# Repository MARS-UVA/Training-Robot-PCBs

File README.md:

# Training-Robot-PCBs

Repository for training robot pcb designs and schematics

### <ins> STATUS <ins/>
Original footprints were created for motor driver and power delivery breakout boards. PCB layout must be done next.

### <ins> CURRENT SIMPLE DESIGN <ins/>

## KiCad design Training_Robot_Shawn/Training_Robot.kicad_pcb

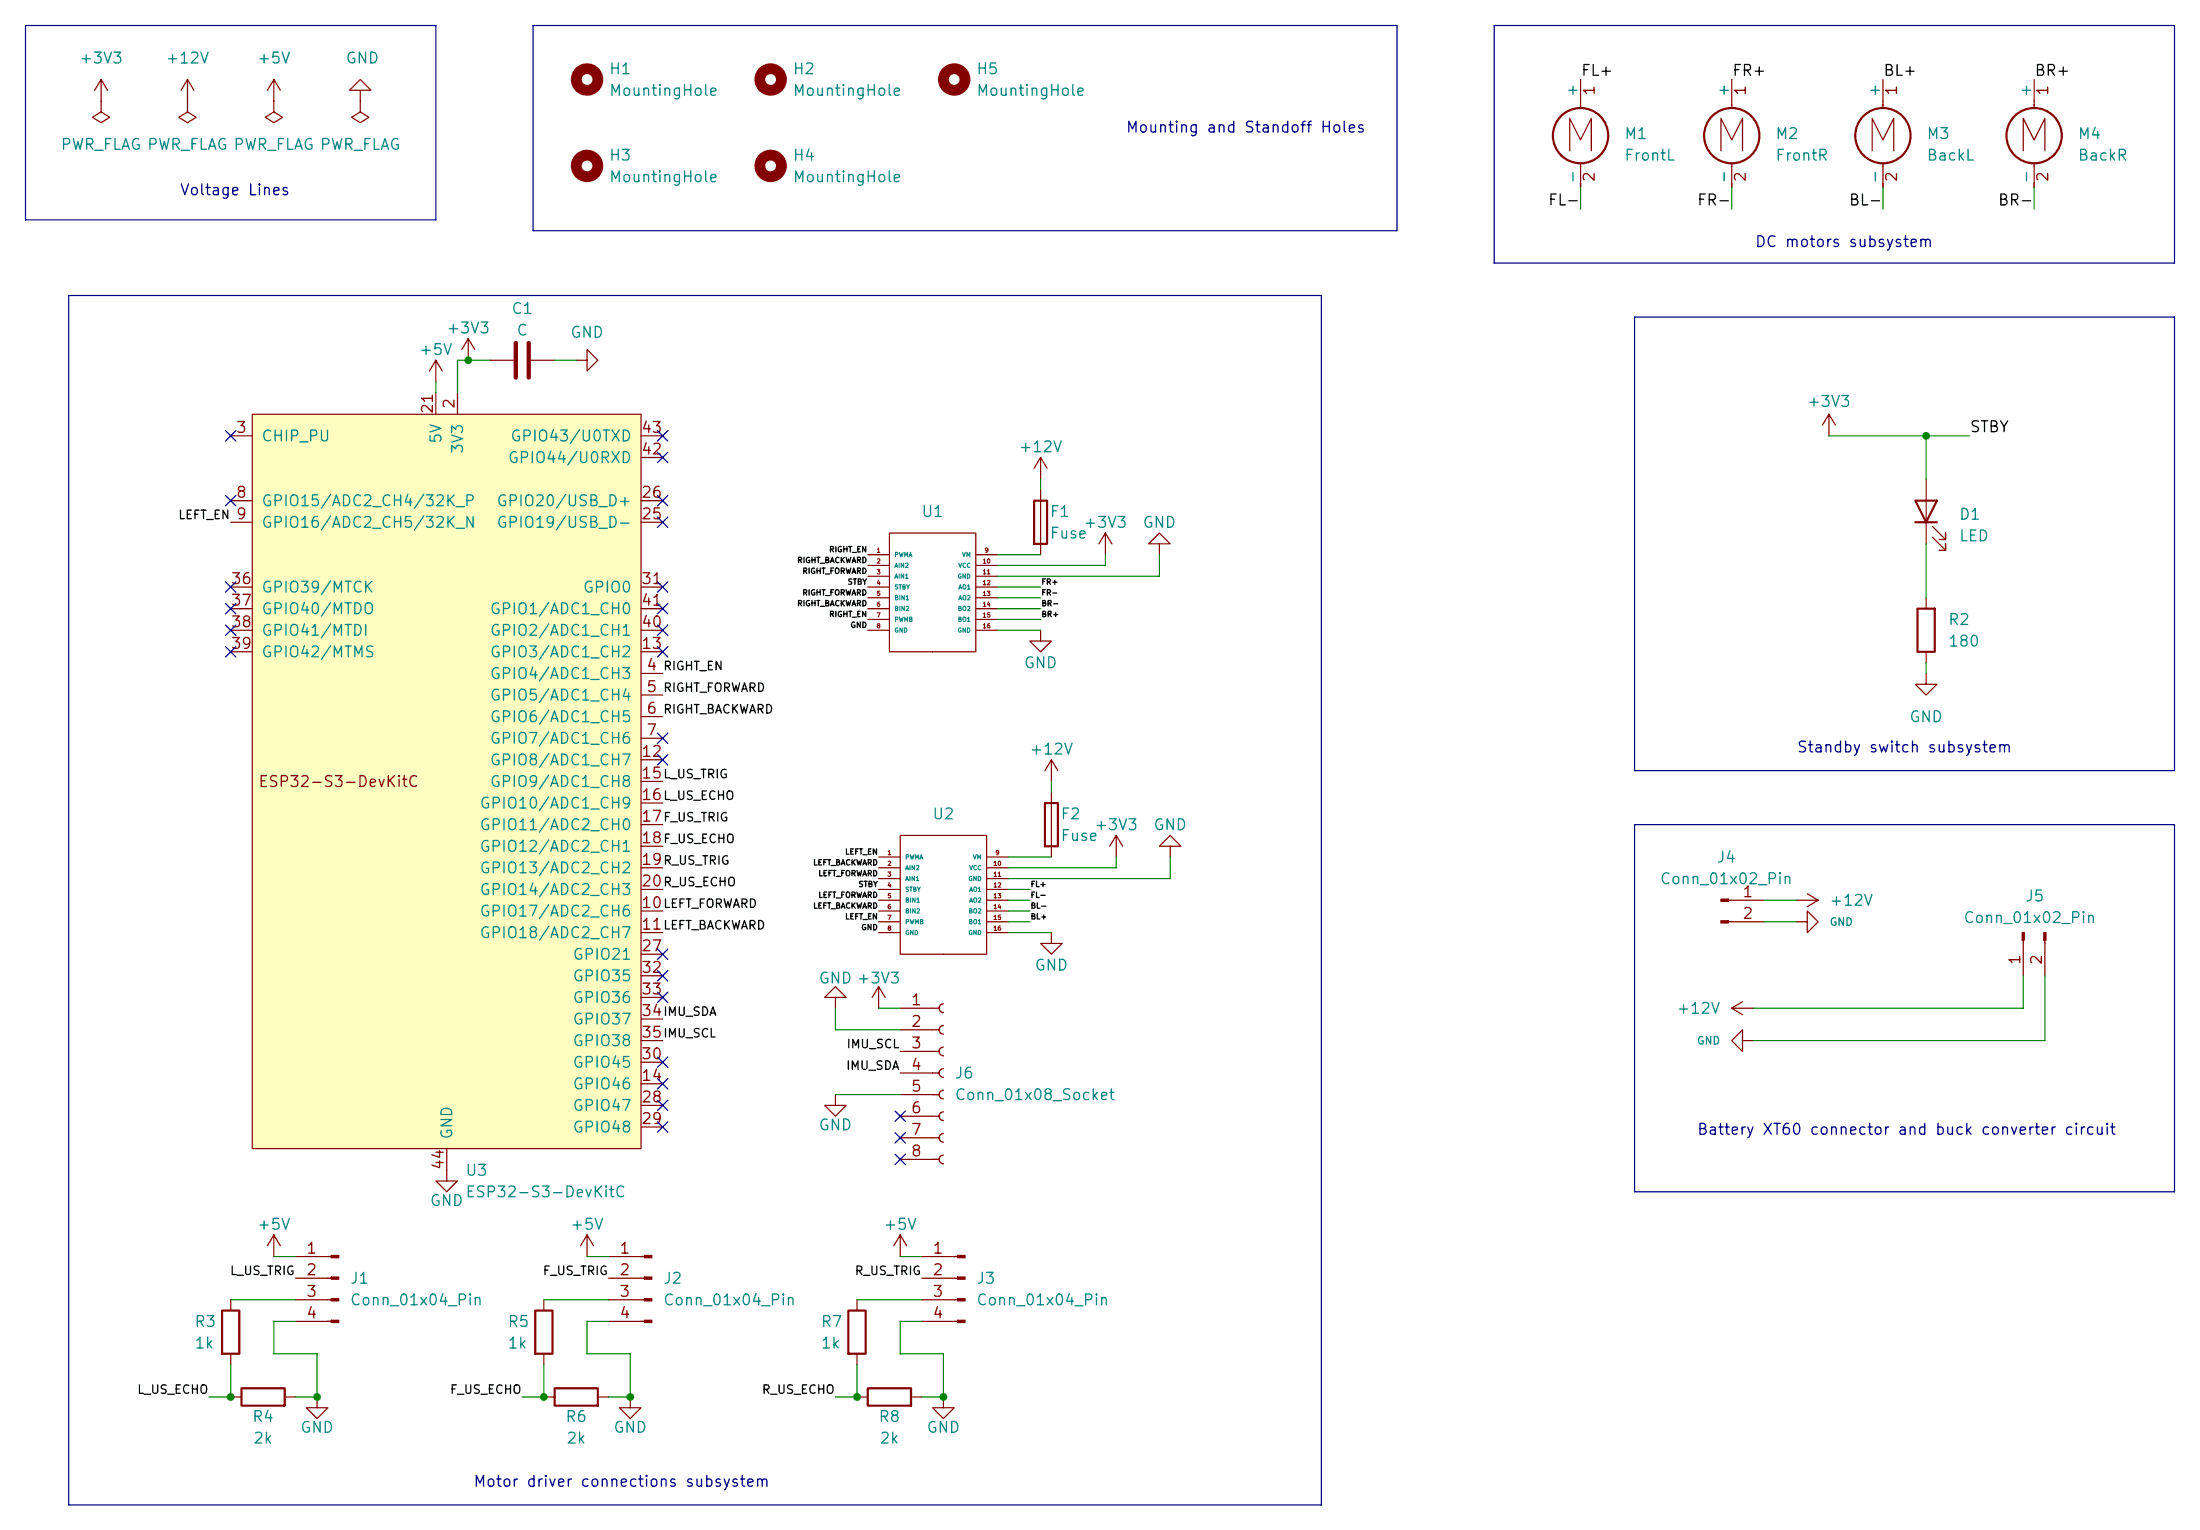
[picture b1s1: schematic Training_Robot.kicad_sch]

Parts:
C1: C; C_Disc_D4.3mm_W1.9mm_P5.00mm
D1: LED; LED_D3.0mm
F1, F2: Fuse; 01530008Z Fuse Holder
H1, H2, H3, H4: MountingHole; MountingHole_6.5mm
H5: MountingHole; MountingHole_4.5mm
J1, J2, J3: Conn_01x04_Pin; JST_XH_B4B-XH-A_1x04_P2.50mm_Vertical
J4: Conn_01x02_Pin; Amass XT60PW
J5: Conn_01x02_Pin; TerminalBlock_Phoenix_MKDS-1,5-2_1x02_P5.00mm_Horizontal
J6: Conn_01x08_Socket; PinSocket_1x08_P2.54mm_Vertical
M1: FrontL; TerminalBlock_Phoenix_MKDS-1,5-2_1x02_P5.00mm_Horizontal
M2: FrontR; TerminalBlock_Phoenix_MKDS-1,5-2_1x02_P5.00mm_Horizontal
M3: BackL; TerminalBlock_Phoenix_MKDS-1,5-2_1x02_P5.00mm_Horizontal
M4: BackR; TerminalBlock_Phoenix_MKDS-1,5-2_1x02_P5.00mm_Horizontal
R2: 180; R_Axial_DIN0204_L3.6mm_D1.6mm_P7.62mm_Horizontal
R3, R5, R7: 1k; R_Axial_DIN0204_L3.6mm_D1.6mm_P7.62mm_Horizontal
R4, R6, R8: 2k; R_Axial_DIN0204_L3.6mm_D1.6mm_P7.62mm_Horizontal
U1, U2: TB6612FNG Breakout
U3: ESP32-S3-DevKitC

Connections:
+3V3: C1.1, D1.2 (A), J6.1, U1.4 (STBY), U1.10 (VCC), U2.4 (STBY), U2.10 (VCC), U3.1 (3V3), U3.2 (3V3)
+5V: J1.1, J2.1, J3.1, U3.21 (5V)
+12V: F1.1, F2.1, J4.1, J5.1
/BL+: M3.1 (+), U2.15 (BO1)
/BL-: M3.2 (-), U2.14 (BO2)
/BR+: M4.1 (+), U1.15 (BO1)
/BR-: M4.2 (-), U1.14 (BO2)
/FL+: M1.1 (+), U2.12 (AO1)
/FL-: M1.2 (-), U2.13 (AO2)
/FR+: M2.1 (+), U1.12 (AO1)
/FR-: M2.2 (-), U1.13 (AO2)
/F_US_ECHO: R5.2, R6.1, U3.18 (GPIO12/ADC2_CH1)
/F_US_TRIG: J2.2, U3.17 (GPIO11/ADC2_CH0)
/IMU_SCL: J6.3, U3.35 (GPIO38)
/IMU_SDA: J6.4, U3.34 (GPIO37)
/LEFT_BACKWARD: U2.2 (AIN2), U2.6 (BIN2), U3.11 (GPIO18/ADC2_CH7)
/LEFT_EN: U2.1 (PWMA), U2.7 (PWMB), U3.9 (GPIO16/ADC2_CH5/32K_N)
/LEFT_FORWARD: U2.3 (AIN1), U2.5 (BIN1), U3.10 (GPIO17/ADC2_CH6)
/L_US_ECHO: R3.2, R4.1, U3.16 (GPIO10/ADC1_CH9)
/L_US_TRIG: J1.2, U3.15 (GPIO9/ADC1_CH8)
/RIGHT_BACKWARD: U1.2 (AIN2), U1.6 (BIN2), U3.6 (GPIO6/ADC1_CH5)
/RIGHT_EN: U1.1 (PWMA), U1.7 (PWMB), U3.4 (GPIO4/ADC1_CH3)
/RIGHT_FORWARD: U1.3 (AIN1), U1.5 (BIN1), U3.5 (GPIO5/ADC1_CH4)
/R_US_ECHO: R7.2, R8.1, U3.20 (GPIO14/ADC2_CH3)
/R_US_TRIG: J3.2, U3.19 (GPIO13/ADC2_CH2)
GND: C1.2, J1.4, J2.4, J3.4, J4.2, J5.2, J6.2, J6.5, R2.1, R4.2, R6.2, R8.2, U1.8 (GND), U1.11 (GND), U1.16 (GND), U2.8 (GND), U2.11 (GND), U2.16 (GND), U3.22 (GND), U3.23 (GND), U3.24 (GND), U3.44 (GND)
unnamed: D1.1 (K), R2.2
unnamed: J1.3, R3.1
unnamed: J2.3, R5.1
unnamed: J3.3, R7.1
unnamed: F1.2, U1.9 (VM)
unnamed: F2.2, U2.9 (VM)

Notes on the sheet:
Mounting and Standoff Holes
Voltage Lines
DC motors subsystem
Standby switch subsystem
Battery XT60 connector and buck converter circuit
Motor driver connections subsystem

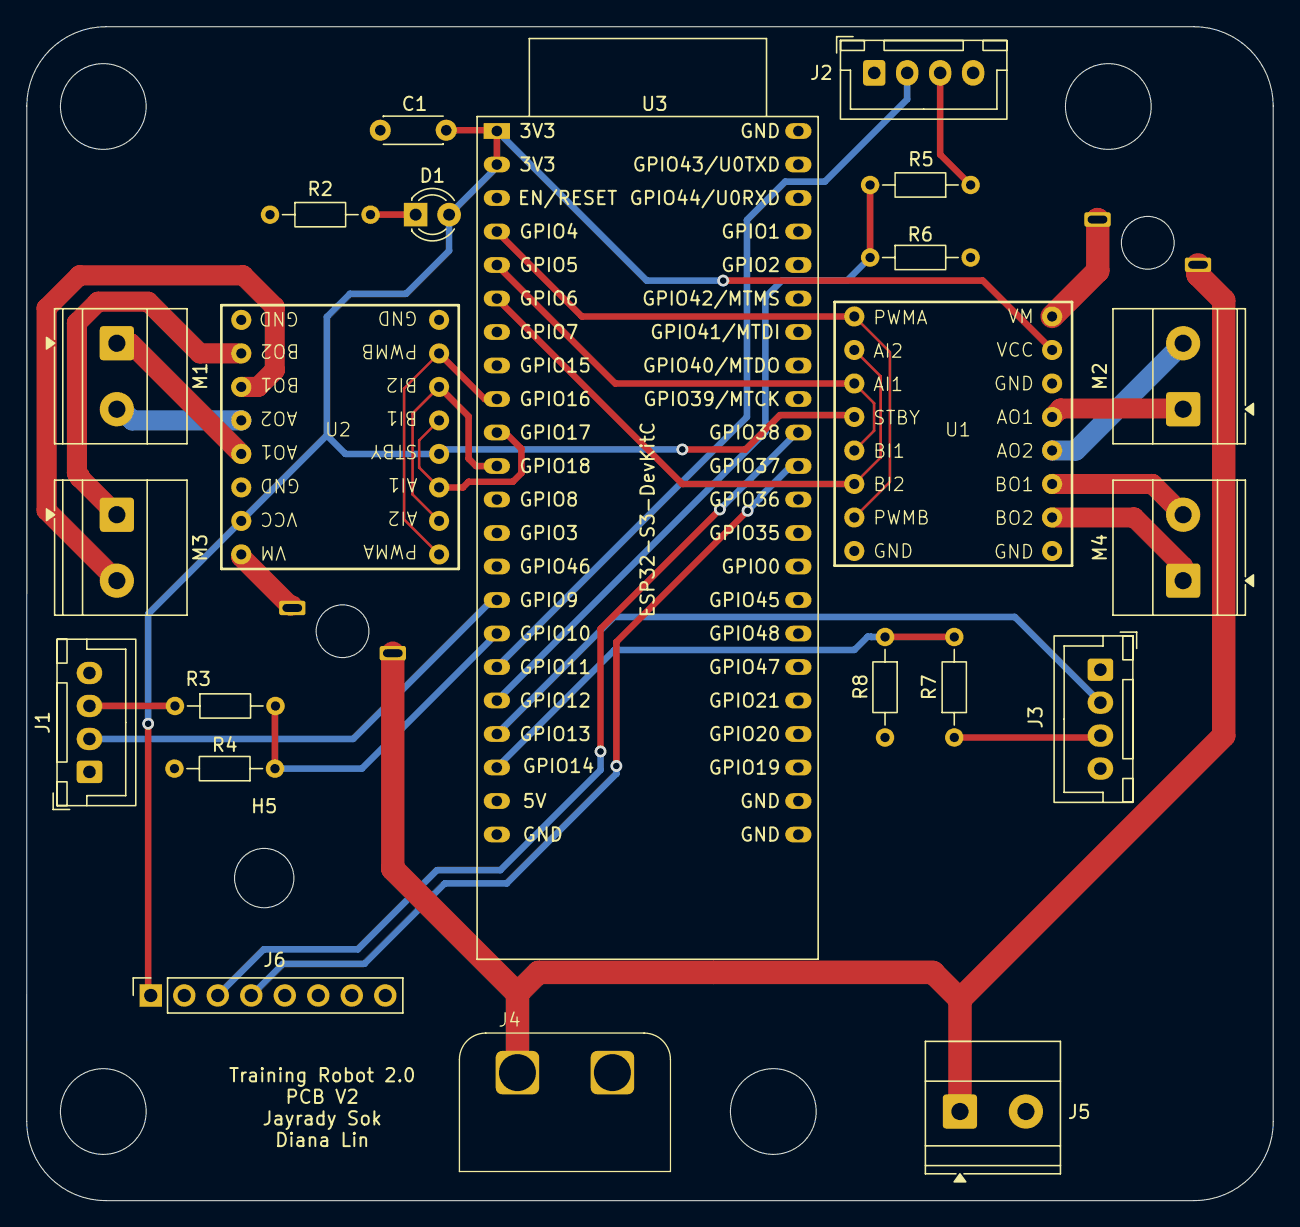
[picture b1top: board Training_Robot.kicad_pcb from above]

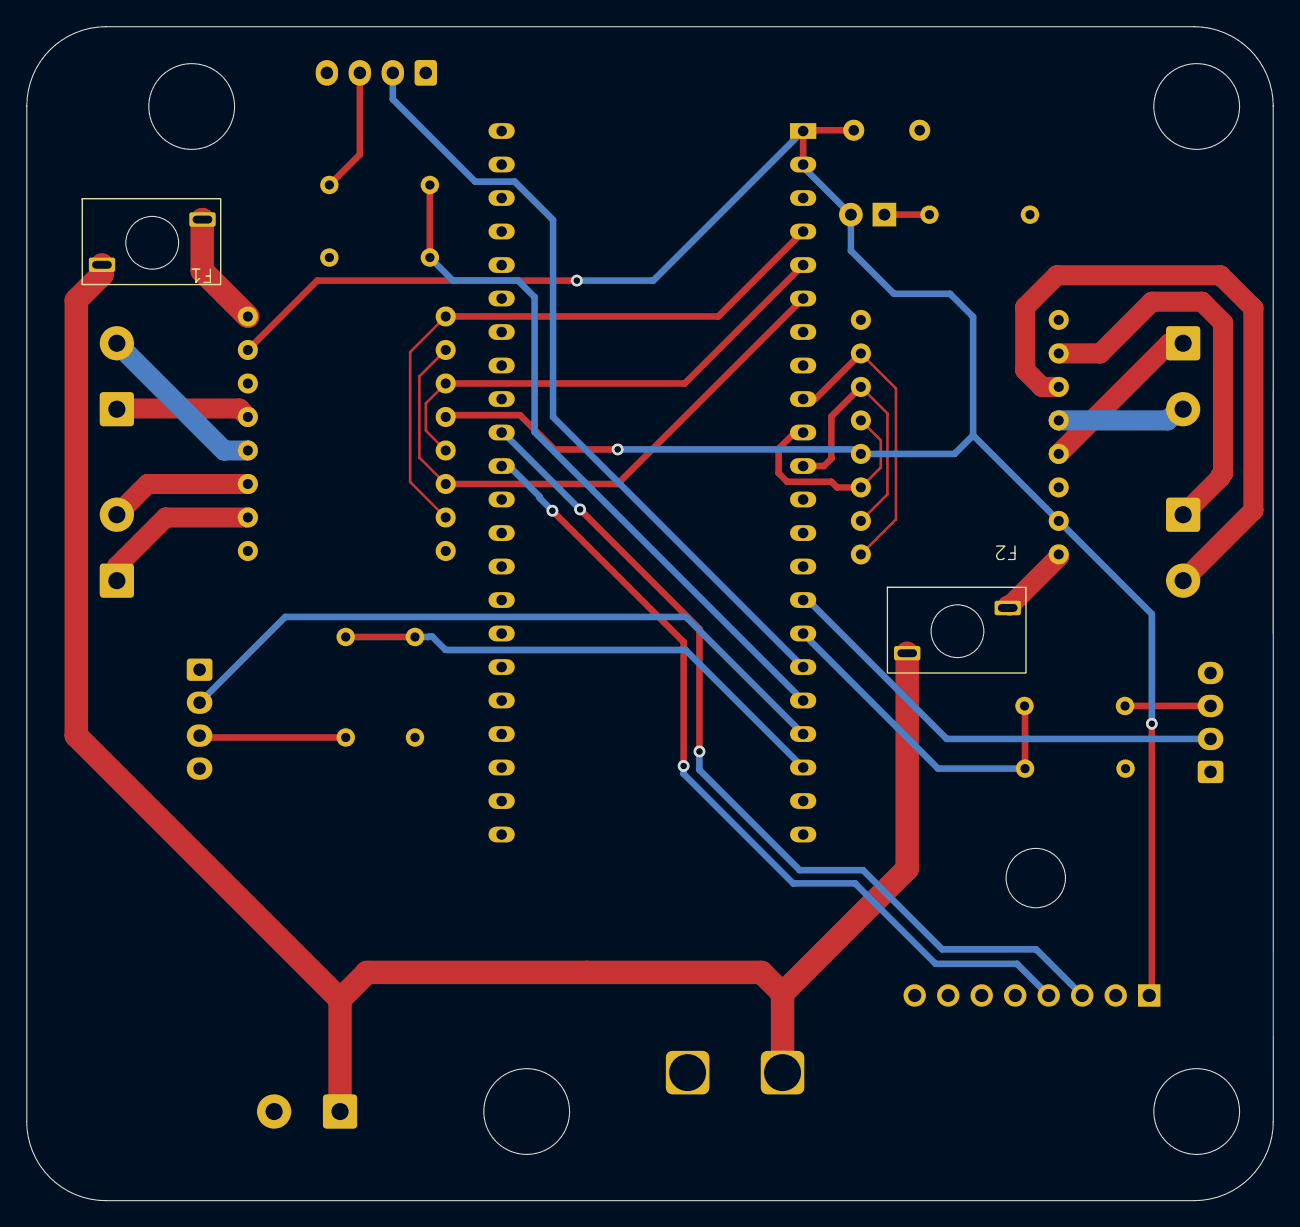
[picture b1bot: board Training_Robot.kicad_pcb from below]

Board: 4 copper layers, 94.5 x 89.0 mm, 29 parts (4 on the bottom side), 32 nets.

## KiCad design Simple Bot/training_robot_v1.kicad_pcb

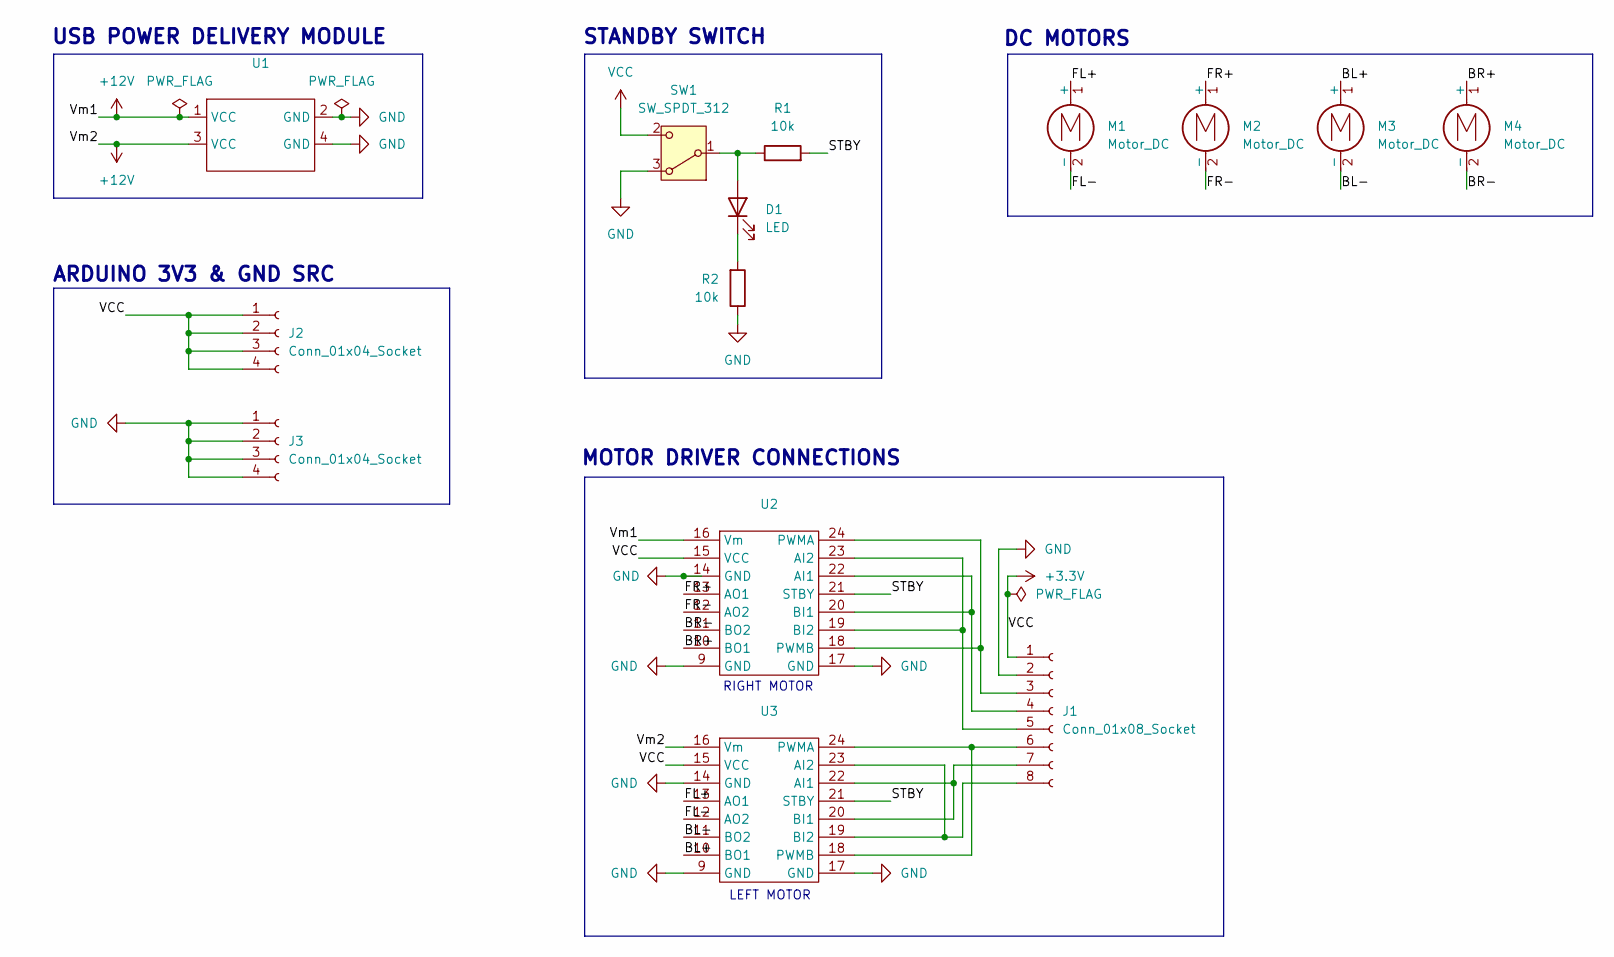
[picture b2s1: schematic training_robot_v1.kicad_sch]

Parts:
D1: LED; LED_D3.0mm
J1: Conn_01x08_Socket; PinSocket_1x08_P2.54mm_Vertical
J2, J3: Conn_01x04_Socket; PinSocket_1x04_P2.54mm_Vertical
M1, M2, M3, M4: Motor_DC; TerminalBlock_Xinya_XY308-2.54-2P_1x02_P2.54mm_Horizontal
R1, R2: 10k; R_Axial_DIN0204_L3.6mm_D1.6mm_P5.08mm_Horizontal
SW1: SW_SPDT_312; SW_Slide_SPDT_Straight_CK_OS102011MS2Q
U1: PD Module
U2, U3: TB_breakout_motor_driver

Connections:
+3.3V: J1.1, J2.1, J2.2, J2.3, J2.4, SW1.2 (C), U2.15 (VCC), U3.15 (VCC)
+12V: U1.1 (VCC), U1.3 (VCC), U2.16 (Vm), U3.16 (Vm)
/BL+: M3.1 (+), U3.10 (BO1)
/BL-: M3.2 (-), U3.11 (BO2)
/BR+: M4.1 (+), U2.10 (BO1)
/BR-: M4.2 (-), U2.11 (BO2)
/FL+: M1.1 (+), U3.13 (AO1)
/FL-: M1.2 (-), U3.12 (AO2)
/FR+: M2.1 (+), U2.13 (AO1)
/FR-: M2.2 (-), U2.12 (AO2)
/STBY: R1.2, U2.21 (STBY), U3.21 (STBY)
GND: J1.2, J3.1, J3.2, J3.3, J3.4, R2.1, SW1.3 (A), U1.2 (GND), U1.4 (GND), U2.9 (GND), U2.14 (GND), U2.17 (GND), U3.9 (GND), U3.14 (GND), U3.17 (GND)
unnamed: D1.2 (A), R1.1, SW1.1 (B)
unnamed: D1.1 (K), R2.2
unnamed: J1.3, U2.18 (PWMB), U2.24 (PWMA)
unnamed: J1.4, U2.20 (BI1), U2.22 (AI1)
unnamed: J1.5, U2.19 (BI2), U2.23 (AI2)
unnamed: J1.6, U3.18 (PWMB), U3.24 (PWMA)
unnamed: J1.7, U3.20 (BI1), U3.22 (AI1)
unnamed: J1.8, U3.19 (BI2), U3.23 (AI2)

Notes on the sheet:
LEFT MOTOR
DC MOTORS
RIGHT MOTOR
USB POWER DELIVERY MODULE
STANDBY SWITCH
MOTOR DRIVER CONNECTIONS
ARDUINO 3V3 & GND SRC

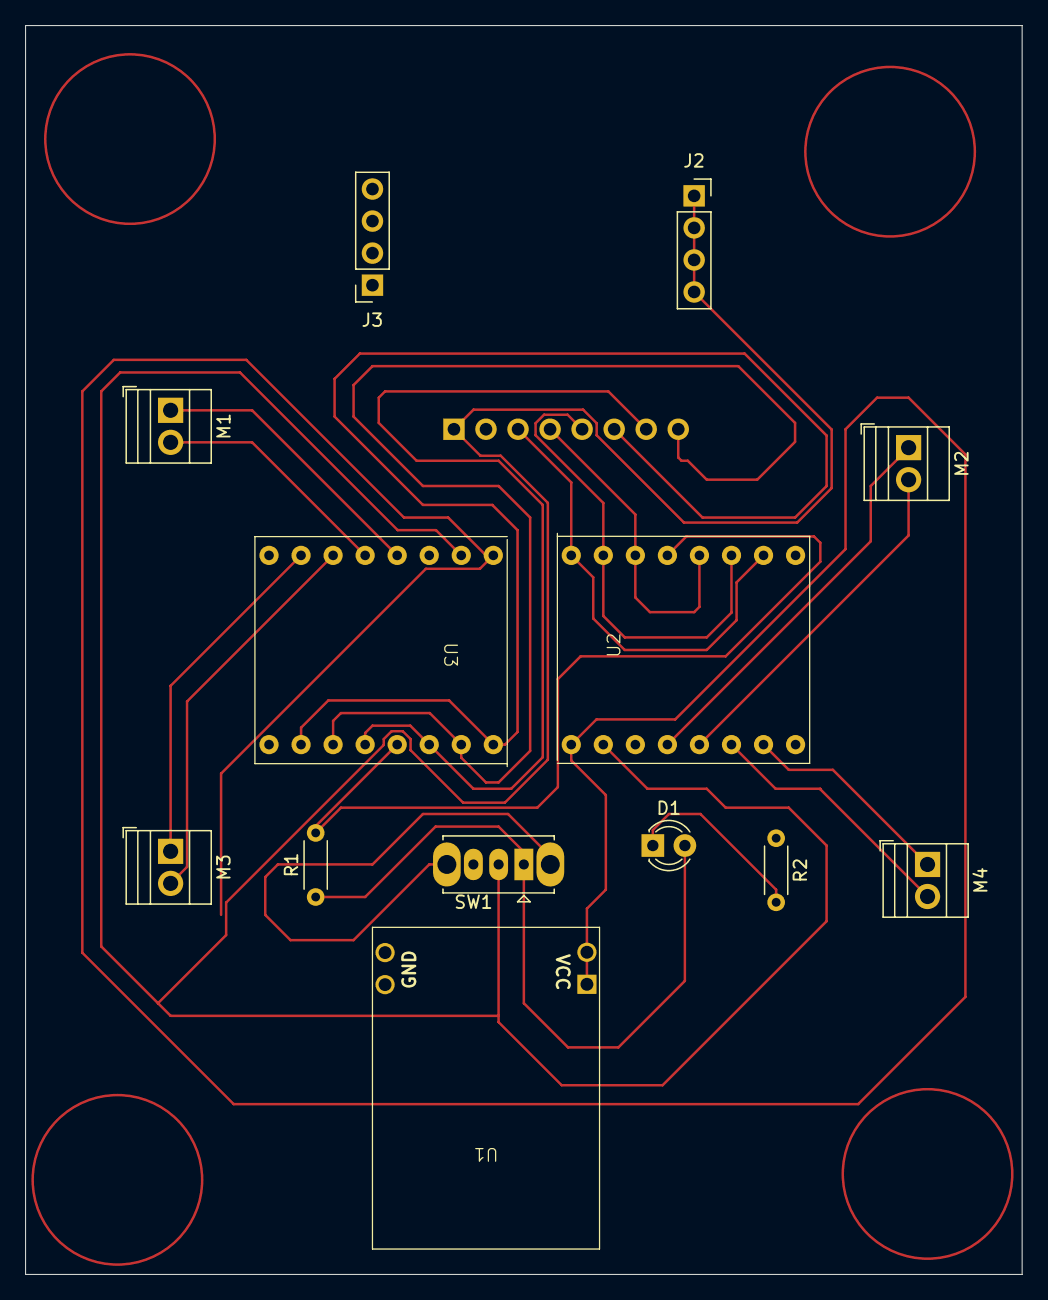
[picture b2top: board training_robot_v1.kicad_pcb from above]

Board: 2 copper layers, 79.0 x 99.0 mm, 14 parts (1 on the bottom side), 20 nets.

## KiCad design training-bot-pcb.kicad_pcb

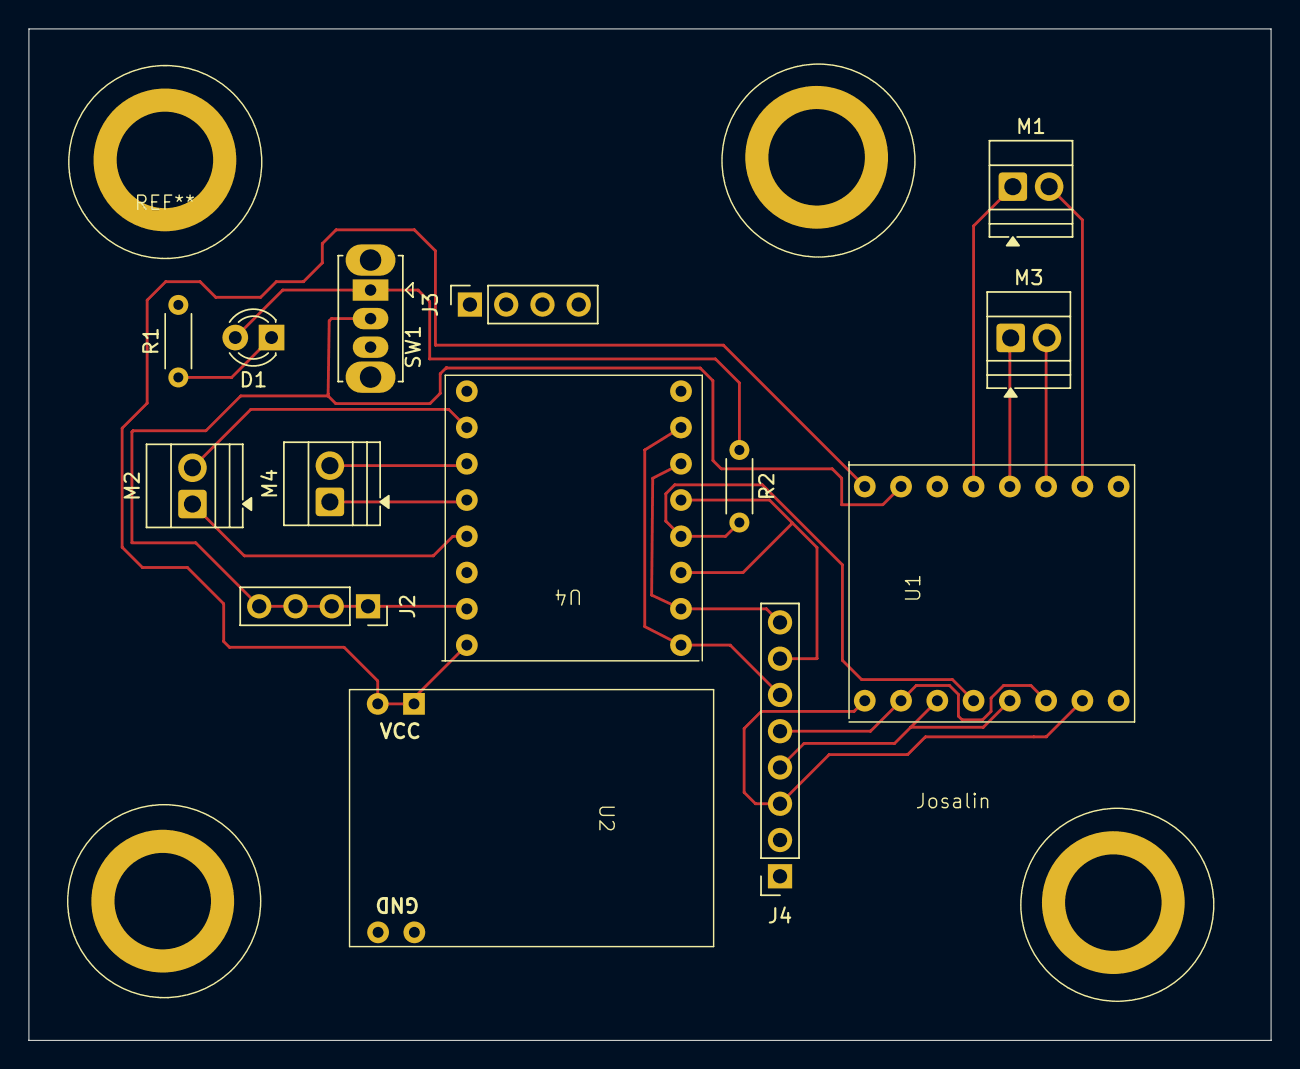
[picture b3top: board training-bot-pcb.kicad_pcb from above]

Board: 2 copper layers, 87.0 x 70.8 mm, 14 parts (0 on the bottom side), 20 nets.

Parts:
D1: LED; LED_D3.0mm
J2, J3: Conn_01x04_Socket; PinSocket_1x04_P2.54mm_Vertical
J4: Conn_01x08_Socket; PinSocket_1x08_P2.54mm_Vertical
M1, M2, M3, M4: Motor_DC; TerminalBlock_Xinya_XY308-2.54-2P_1x02_P2.54mm_Horizontal
R1, R2: R; R_Axial_DIN0204_L3.6mm_D1.6mm_P5.08mm_Horizontal
SW1: SW_SPDT_312; SW_Slide_SPDT_Straight_CK_OS102011MS2Q
U1: L MOTOR DRIVER; TB_breakout_motor_driver
U2: PD module; PD Module
U4: R MOTOR DRIVER; TB_breakout_motor_driver

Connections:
+12V: U1.9 (VM), U2.1 (VCC), U2.2 (VCC), U4.9 (VM)
/BL+: M3.1 (+), U1.13 (AO2)
/BL-: M3.2 (-), U1.14 (BO2)
/BR+: M4.1 (+), U4.13 (AO2)
/BR-: M4.2 (-), U4.14 (BO2)
/FL+: M1.1 (+), U1.12 (AO1)
/FL-: M1.2 (-), U1.15 (BO1)
/FR+: M2.1 (+), U4.12 (AO1)
/FR-: M2.2 (-), U4.15 (BO1)
/STBY: R2.2, U1.4 (STBY), U4.4 (STBY)
GND: J3.1, J3.2, J3.3, J3.4, J4.2, R1.2, SW1.3 (A), U1.8 (GND), U1.11 (GND), U1.16 (GND), U2.3 (GND), U2.4 (GND), U4.8 (GND), U4.11 (GND), U4.16 (GND)
unnamed: D1.2 (A), R2.1, SW1.1 (B)
unnamed: D1.1 (K), R1.1
unnamed: J4.3, U1.1 (PWMA), U1.7 (PWMB)
unnamed: J4.4, U1.3 (AIN1), U1.5 (BIN1)
unnamed: J4.5, U1.2 (AIN2), U1.6 (BIN2)
unnamed: J4.6, U4.1 (PWMA), U4.7 (PWMB)
unnamed: J4.7, U4.3 (AIN1), U4.5 (BIN1)
unnamed: J4.8, U4.2 (AIN2), U4.6 (BIN2)
VCC: J2.1, J2.2, J2.3, J2.4, SW1.2 (C), U1.10 (VCC), U4.10 (VCC)

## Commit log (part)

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2026-01-02 init commit w/ schematic
2026-01-02 Added image
2026-01-02 Add current simple design section to README
2026-01-02 Add status update for PCB design progress
    Added status section to README with current progress.
2026-01-02 Modify headers for STATUS and CURRENT SIMPLE DESIGN
    Updated section headers in README.md to use HTML tags for emphasis.
2026-01-29 Fixed rats nest issue
2026-01-30 Removed schematic details
2026-02-20 Finished folder
2026-02-22 Updated folder
    Changed silkscreen labels
2026-02-23 Updated folder
2026-02-24 uploaded gerber files
2026-02-24 upload pcb and schematic files
2026-02-24 Add drill files to Gerbers zip
2026-02-24 Update Gerber zip file
2026-02-24 Close Kicad
2026-02-25 Updated folder
    Changed mounting hole distance
2026-02-27 Update contstraints
2026-03-04 replaced "simple" sch and pcb files with Josalin's
2026-03-04 accepted changes ig lol
2026-03-04 added git ignore, modified pcb
2026-03-04 changed motor connector footprint and moved output power conn
2026-03-04 moved a tiny bit
2026-03-05 reduced size profile to 3x3 inches between mounting holes (horizontally and vertically)
    reduced from 3x4 in between holes
2026-03-05 corrected direction of motor screw terminals
2026-03-08 git ignore add
2026-03-09 added gerber files for final
